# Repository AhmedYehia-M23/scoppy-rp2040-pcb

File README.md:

# Custom RP2040 Mixed-Signal Measurement PCB

**4-layer RP2040 hardware · KiCad · mixed-signal PCB layout · USB-C · hand assembly · hardware bring-up**

A university PCB-layout and hardware-bring-up project based on **professor-provided electrical schematics** for a custom RP2040 measurement board associated with the Scoppy oscilloscope ecosystem. My work was the **PCB implementation and physical hardware workflow**: placement, 4-layer stack-up and routing, fabrication preparation, hand assembly, bring-up and fault isolation.

| | |
|---|---|
| **Board** | 67 × 50 mm, 4 layers |
| **MCU** | RP2040 with W25Q128 QSPI flash |
| **Layout** | 64 footprints · 597 routed track segments · 58 vias |
| **Internal planes** | GND on In1.Cu · +3V3 on In2.Cu |
| **Academic context** | Materials and Manufacturing of Electronics · Summer Semester 2026 |

### Quick links

- [PCB layout source](hardware/Scoppy.kicad_pcb)
- [PCB layout image](images/pcb-layout.png)
- [Bring-up and debugging notes](docs/bring-up-and-debugging.md)
- [Source attribution](SOURCE_ATTRIBUTION.md)

> The electrical schematics and circuit/component-level design were supplied as course material. They are not redistributed here. The PCB placement, routing, assembly and bring-up documented in this repository are my project work.

## My contribution

- 4-layer PCB stack-up and physical implementation in KiCad
- complete component and footprint placement
- all PCB routing
- internal GND and +3V3 plane implementation
- mixed-signal physical-layout decisions
- board outline and physical organization
- design-rule checking and fabrication preparation
- complete hand assembly and soldering after fabrication
- board bring-up and electrical measurements
- USB-enumeration fault investigation
- power, continuity, USB, boot and clock checks
- root-cause isolation to incomplete RP2040 solder contact
- repair and restoration of USB enumeration

## PCB layout

## Architecture

The supplied course design was organized into hierarchical **Power**, **Digital** and **Analog** schematic sheets. My task was to translate those circuit requirements into a manufacturable 4-layer PCB while managing placement, signal routing, return paths, power distribution and physical board constraints.

## Assembly and bring-up

After fabrication, I assembled and hand-soldered the complete board. The first assembled board powered up but failed to enumerate over USB, including BOOTSEL attempts.

The diagnostic sequence covered:

- 5 V, 3.3 V and RP2040 1.1 V rails
- RUN / BOOTSEL state
- external-flash related circuitry
- USB-C CC configuration
- D+ / D- continuity and short checks
- RP2040 grounding and exposed-pad contact
- 12 MHz crystal network
- physical MCU solder contact

The final root cause was incomplete electrical contact at the RP2040 package. Correcting the solder/contact defect **restored USB enumeration**.

The detailed check sequence and the boundary of the available evidence are documented in [`docs/bring-up-and-debugging.md`](docs/bring-up-and-debugging.md).

## Public project files

```text
hardware/
├── Scoppy.kicad_pro
├── Scoppy.kicad_pcb
├── fp-lib-table
└── LIB/
    └── footprints/
        └── DME_Template.pretty/

docs/
└── bring-up-and-debugging.md

images/
├── architecture.svg
├── pcb-layout.png
└── pcb-3d-view.png
```

Professor-provided schematic source and symbol/cache files are intentionally excluded from the public portfolio repository. Per-user KiCad state files, lock files, autosaves, backups and operating-system metadata are also excluded.

## Tools and skills

`KiCad` · `RP2040` · `4-Layer PCB Layout` · `Component Placement` · `Manual PCB Assembly & Soldering` · `Mixed-Signal PCB Routing` · `Internal Power/Ground Planes` · `USB-C` · `Hardware Bring-Up` · `Fault Isolation` · `Continuity & Voltage Measurement`

## Scoppy attribution

**Scoppy** is a separate project maintained by **fhdm-dev**. I did not develop the Scoppy Android application or its firmware. This repository presents my university PCB-layout, assembly and hardware-bring-up work and is not affiliated with or endorsed by the original Scoppy maintainers.

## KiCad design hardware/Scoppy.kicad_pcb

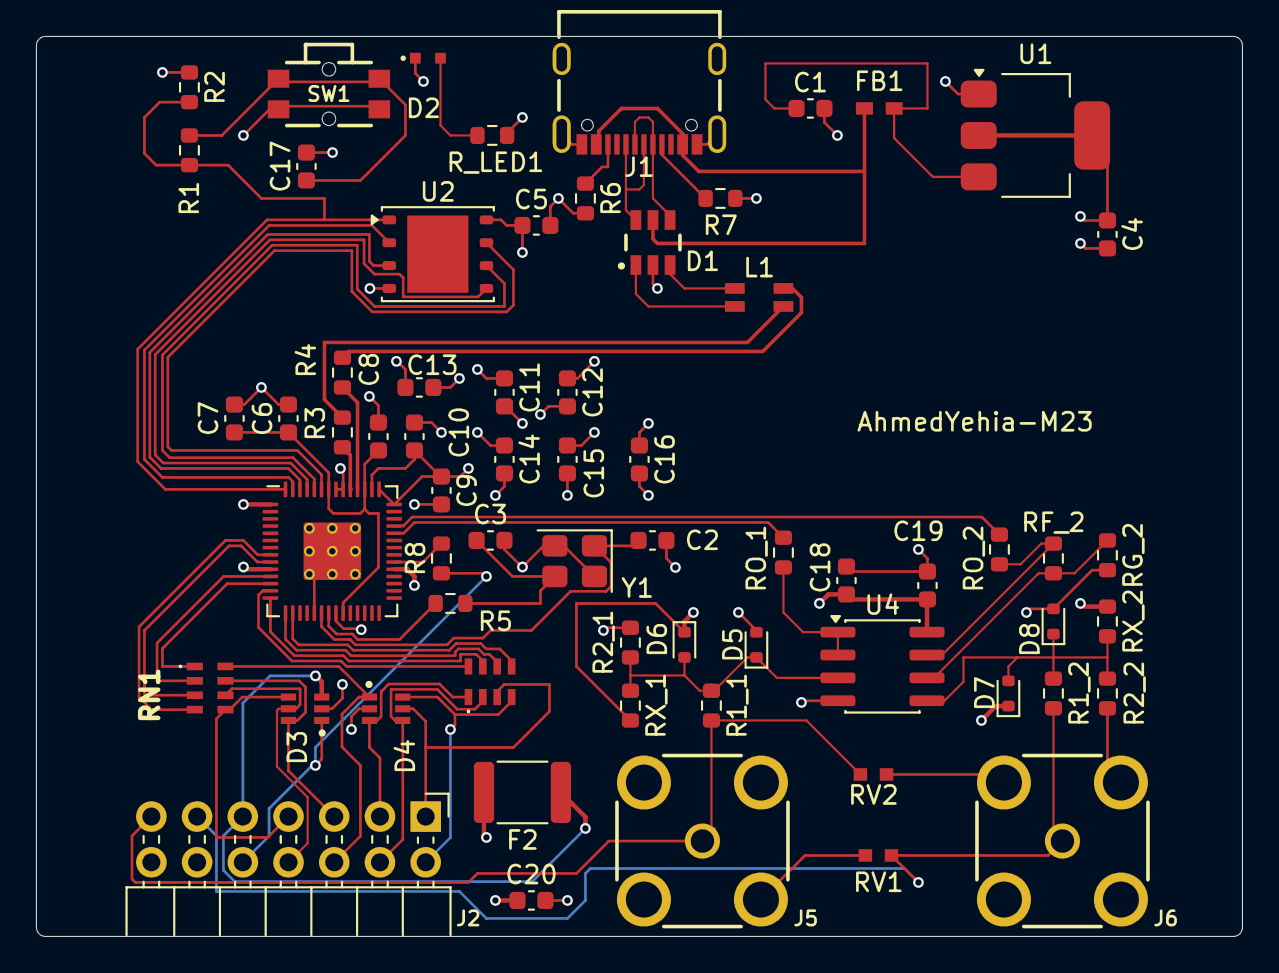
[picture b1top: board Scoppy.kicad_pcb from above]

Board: 4 copper layers, 67.0 x 50.0 mm, 64 parts (0 on the bottom side), 54 nets.

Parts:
C1, C4: 10u; C_0603_1608Metric
C2, C3: 15p; C_0603_1608Metric
C5, C6, C7, C9, C11, C12, C13, C14, C15, C16, C17: 100n; C_0603_1608Metric
C8, C10: 1u; C_0603_1608Metric
C18: 10uf; C_0603_1608Metric
C19: 100nf; C_0603_1608Metric
C20: 22u; C_0603_1608Metric
D1: 5V; WE-TVS_SOT23-6L
D2: Bright Green, 2V, 140°; WL-SMSW_0603_L1.6W0.98H0.8
D3, D4: 5V; WE-TVS_SC70-6L
D5, D6, D7, D8: 1N4148; D_SOD-523
F2: 300mA PPTC; Fuse_1812_4532Metric
FB1: 600Ω; WE-CBF_0603_L1.6W0.8H0.8_HC
J1: 629722000214
J2: Conn_02x07_Odd_Even; PinHeader_2x07_P2.54mm_Horizontal
J5, J6: 60711002241501
L1: 90Ω @100MHz; WE-CNSW_1206
R1, R5: 1k; R_0603_1608Metric
R1_1, R2_1: 470k; R_0603_1608Metric
R1_2: 330k; R_0603_1608Metric
R2: 10k; R_0603_1608Metric
R2_2: 680k; R_0603_1608Metric
R3, R4: 27; R_0603_1608Metric
R6, R7: 5k1; R_0603_1608Metric
R8: 47; R_0603_1608Metric
RF_2: 18k; R_0603_1608Metric
RG_2: 10k; R_0603_1608Metric
RN1, RN2: CAY16-470J4LF; CAY16470J4LF
RO_1, RO_2: 100; R_0603_1608Metric
RV1, RV2: 12VDC, 5pF; WE-VE_0603
RX_1: 220k; R_0603_1608Metric
RX_2: 1M; R_0603_1608Metric
R_LED1: 1k; R_0603_1608Metric
SW1: 436351045816
U1: NCP1117-3.3_SOT223; SOT-223-3_TabPin2
U2: W25Q128JVS; WSON-8-1EP_6x5mm_P1.27mm_EP3.4x4.3mm
U3: RP2040; RP2040-QFN-56
U4: MCP6002-xSN; SOIC-8_3.9x4.9mm_P1.27mm
Y1: ABM8-272-T3; Crystal_SMD_3225-4Pin_3.2x2.5mm

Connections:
+1V1: C6.1, C7.1, C8.1, U3.23 (DVDD), U3.45 (VREG_VOUT), U3.50 (DVDD)
+3V3: C4.1, C5.1, C9.1, C10.1, C11.1, C12.1, C13.1, C14.1, C15.1, C16.1, C18.1, C19.2, C20.1, D6.1 (K), D7.1 (K), F2.2, R2.1, RX_1.2, RX_2.1, R_LED1.2, U1.2 (VO), U2.8 (VCC), U3.1 (IOVDD), U3.10 (IOVDD), U3.22 (IOVDD), U3.33 (IOVDD), U3.42 (IOVDD), U3.43 (ADC_AVDD), U3.44 (VREG_IN), U3.48 (USB_VDD), U3.49 (IOVDD), U4.8 (V+)
/Analog/CH1+: J2.13, J5.1 (Signal), R1_1.2, RV2.2
/Analog/CH2+: J2.11, J6.1 (Signal), R1_2.2, RV1.2
/Analog/GPIO26_ADC0: RO_1.2, U3.38 (GPIO26_ADC0)
/Analog/GPIO27_ADC1: RO_2.2, U3.39 (GPIO27_ADC1)
/Digital/3V3_fused: D3.3 (I/O_2), F2.1, J2.9
/Digital/AWG: D3.1 (I/O_1), J2.10, R8.1
/Digital/DI0: D3.4 (I/O_3), J2.7, RN1.5
/Digital/DI1: D3.5 (I/O_4), J2.8, RN1.6
/Digital/DI2: D3.6 (I/O_5), J2.5, RN1.7
/Digital/DI3: D4.1 (I/O_1), J2.6, RN1.8
/Digital/DI4: D4.3 (I/O_2), J2.3, RN2.1
/Digital/DI5: D4.4 (I/O_3), J2.4, RN2.2
/Digital/DI6: D4.5 (I/O_4), J2.1, RN2.3
/Digital/DI7: D4.6 (I/O_5), J2.2, RN2.4
/Digital/GPIO6: RN1.4, U3.8 (GPIO6)
/Digital/GPIO7: RN1.3, U3.9 (GPIO7)
/Digital/GPIO8: RN1.2, U3.11 (GPIO8)
/Digital/GPIO9: RN1.1, U3.12 (GPIO9)
/Digital/GPIO10: RN2.8, U3.13 (GPIO10)
/Digital/GPIO11: RN2.7, U3.14 (GPIO11)
/Digital/GPIO12: RN2.6, U3.15 (GPIO12)
/Digital/GPIO13: RN2.5, U3.16 (GPIO13)
/Digital/GPIO22: R8.2, U3.34 (GPIO22)
/Digital/QSPI_SCLK: U2.6 (CLK), U3.52 (QSPI_SCLK)
/Digital/QSPI_SD0: U2.5 (DI/IO_{0}), U3.53 (QSPI_SD0)
/Digital/QSPI_SD1: U2.2 (DO/IO_{1}), U3.55 (QSPI_SD1)
/Digital/QSPI_SD2: U2.3 (~WP/IO_{2}), U3.54 (QSPI_SD2)
/Digital/QSPI_SD3: U2.7 (~HOLD/~RESET/IO_{3}), U3.51 (QSPI_SD3)
/Digital/QSPI_SS: R1.1, R2.2, U2.1 (~CS), U3.56 (QSPI_SS)
/Digital/USB_D+: L1.3, R3.1
/Digital/USB_D-: L1.2, R4.1
/Digital/XIN: C2.1, U3.20 (XIN), Y1.1
/Digital/XOUT: R5.1, U3.21 (XOUT)
/Digital/usbD+: R3.2, U3.47 (USB_DP)
/Digital/usbD-: R4.2, U3.46 (USB_DM)
/Digital/~USB_BOOT: C17.1, R1.2, SW1.B1, SW1.B2
/Power/esd_safeD+: D1.1 (I/O_1), L1.4
/Power/esd_safeD-: D1.3 (I/O_2), L1.1
/Power/unprotectedD+: D1.6 (I/O_1), J1.A6 (D+1), J1.B6 (D+2)
/Power/unprotectedD-: D1.4 (I/O_2), J1.A7 (D-1), J1.B7 (D-2)
GND: C1.2, C2.2, C3.2, C4.2, C5.2, C6.2, C7.2, C8.2, C9.2, C10.2, C11.2, C12.2, C13.2, C14.2, C15.2, C16.2, C17.2, C18.2, C19.1, C20.2, D1.2 (GND), D2.1 (K), D3.2 (GND), D4.2 (GND), D5.2 (A), D8.2 (A), J1.A1/B12 (GND), J1.A12/B1 (GND), J1.Shell (Shield), J2.12, J2.14, J5.2 (GND), J5.3 (GND), J5.4 (GND), J5.5 (GND), J6.2 (GND), J6.3 (GND), J6.4 (GND), J6.5 (GND), R2_1.2, R2_2.1, R6.2, R7.2, RG_2.2, RV1.1, RV2.1, SW1.A1, SW1.A2, U1.1 (GND), U2.4 (GND), U3.19 (TESTEN), U3.57 (GND), U4.4 (V-), Y1.2, Y1.4
unnamed: C3.1, R5.2, Y1.3
unnamed: D2.2 (A), R_LED1.1
unnamed: D5.1 (K), D6.2 (A), R1_1.1, R2_1.1, RX_1.1, U4.3 (+)
unnamed: D7.2 (A), D8.1 (K), R1_2.1, R2_2.2, RX_2.2, U4.5 (+)
unnamed: J1.A5 (CC1), R7.1
unnamed: J1.B5 (CC2), R6.1
unnamed: RF_2.2, RO_2.1, U4.7
unnamed: C1.1, FB1.2, U1.3 (VI)
unnamed: RO_1.1, U4.1, U4.2 (-)
unnamed: RF_2.1, RG_2.1, U4.6 (-)
VBUS: D1.5 (VDD), FB1.1, J1.A4/B9 (VBUS), J1.A9/B4 (VBUS)
